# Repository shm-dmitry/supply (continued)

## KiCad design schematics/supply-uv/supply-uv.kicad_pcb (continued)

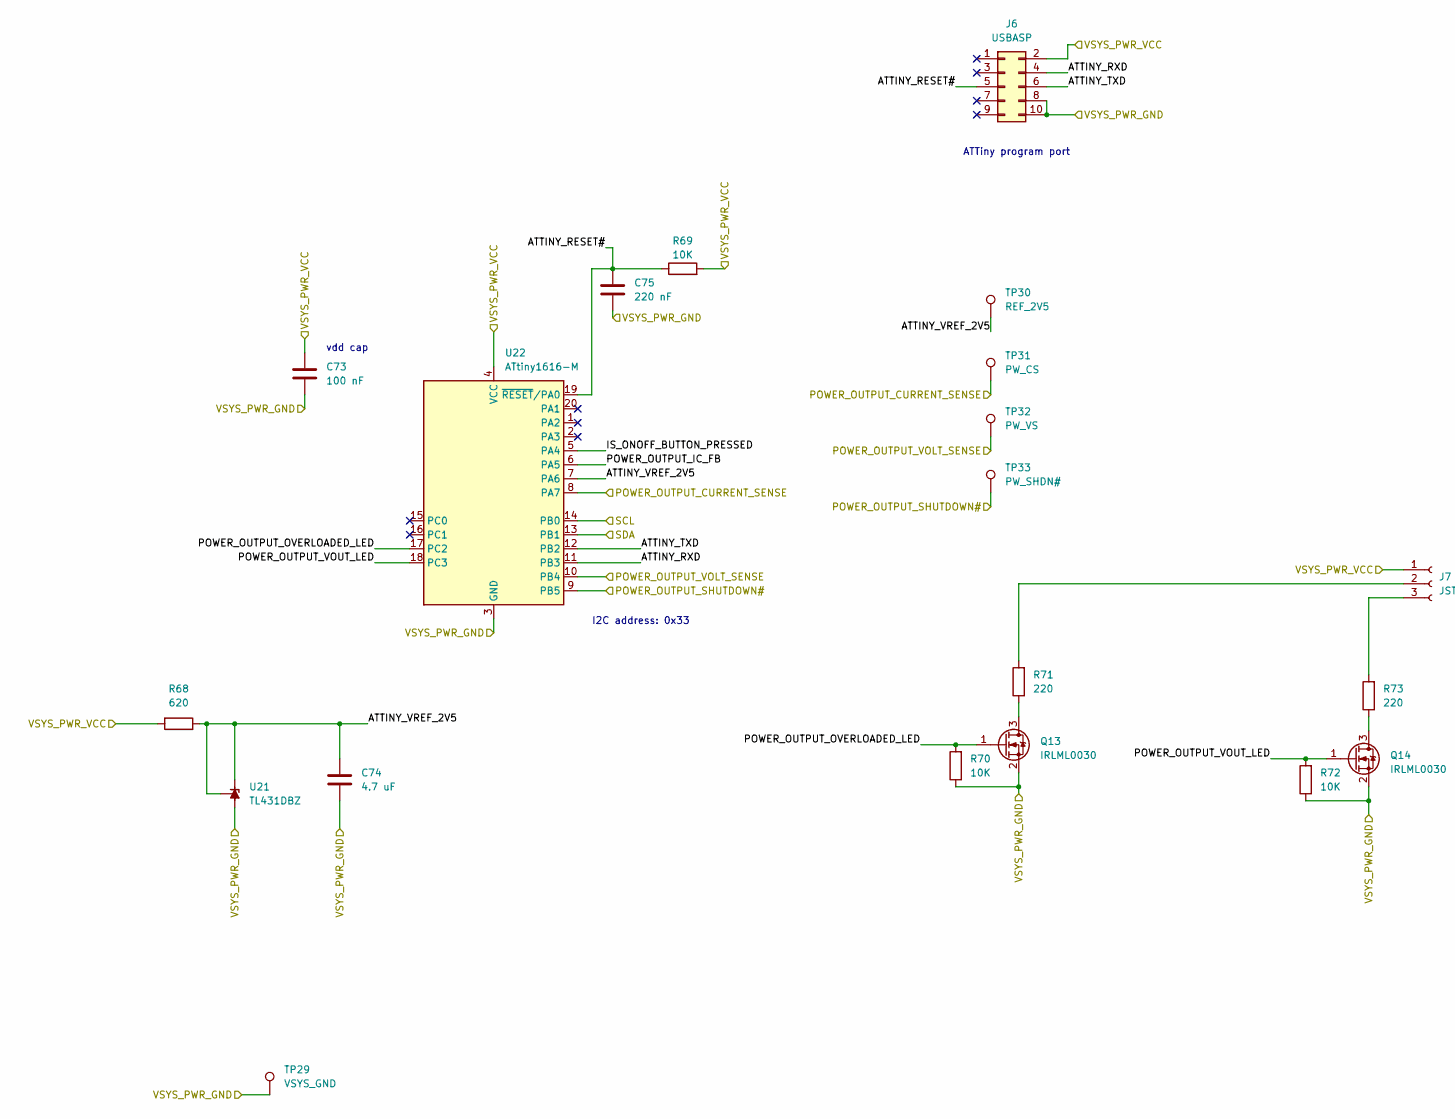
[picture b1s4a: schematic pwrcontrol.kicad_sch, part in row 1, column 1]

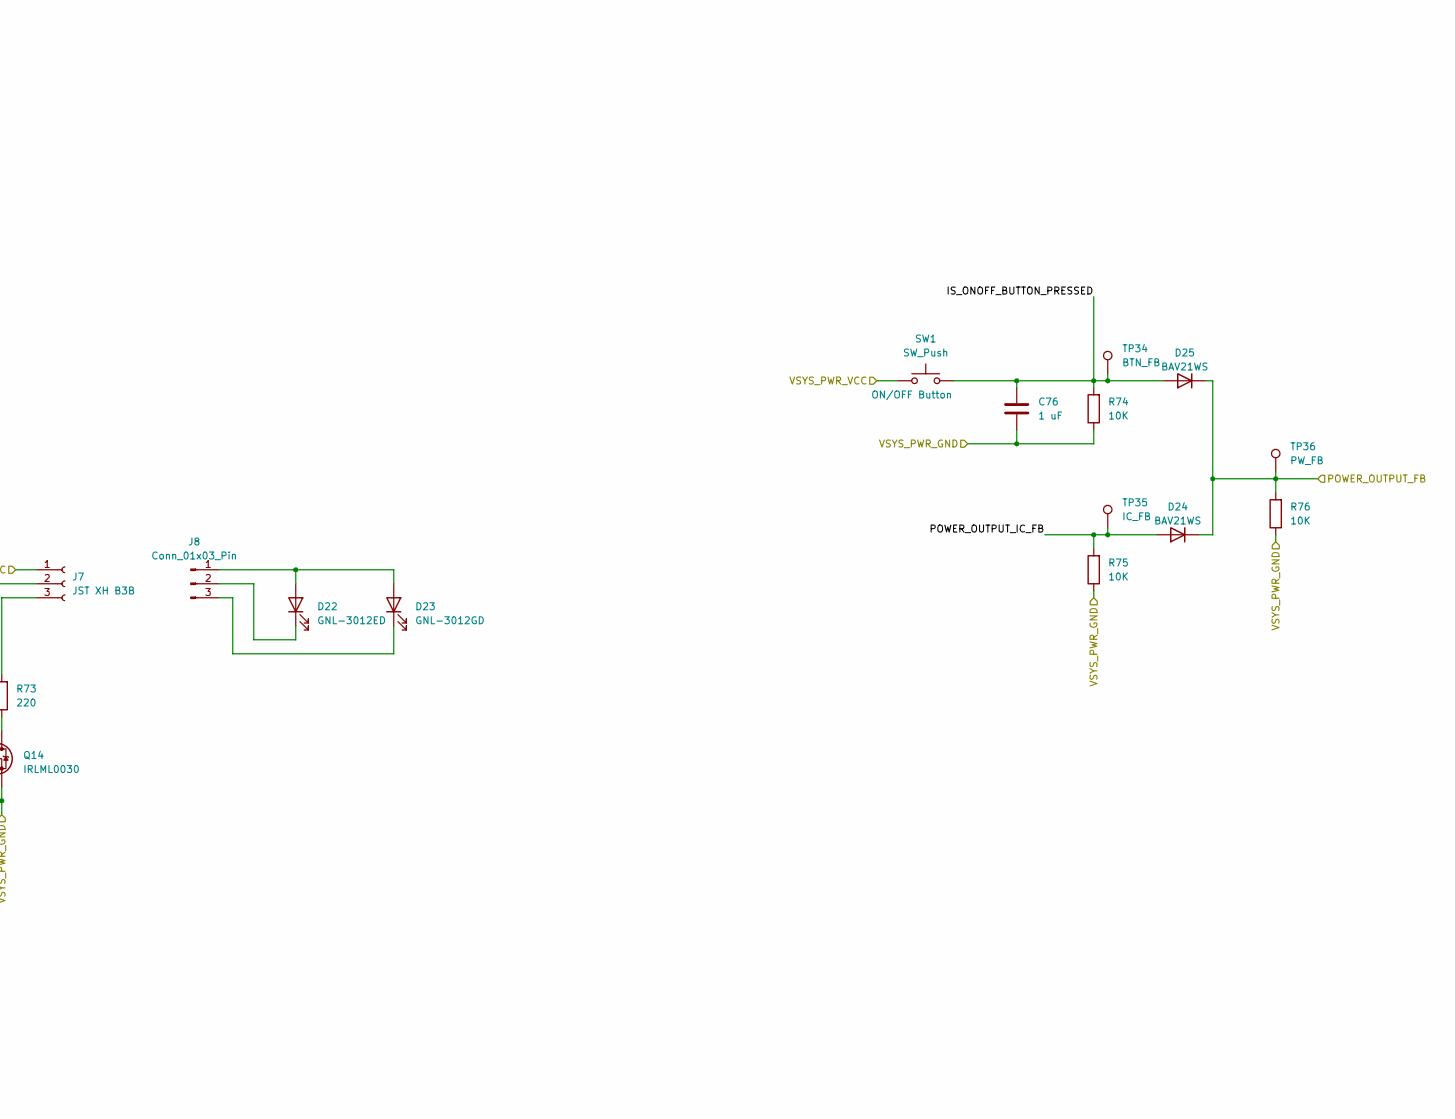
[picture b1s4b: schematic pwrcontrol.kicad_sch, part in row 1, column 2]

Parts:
C73: 100 nF; C_0603_1608Metric
C74: 4.7 uF; C_0603_1608Metric
C75: 220 nF; C_0603_1608Metric
C76: 1 uF; C_0603_1608Metric
D22: GNL-3012ED; JST_XH_B2B-XH-A_1x02_P2.50mm_Vertical
D23: GNL-3012GD; JST_XH_B2B-XH-A_1x02_P2.50mm_Vertical
D24, D25: BAV21WS; D_SOD-323F
J6: USBASP; DC3-2x05_p2.54
J7: JST XH B3B; JST_XH_B3B-XH-A_1x03_P2.50mm_Vertical
J8: Conn_01x03_Pin
Q13, Q14: IRLML0030; SOT-23
R68: 620; R_0805_2012Metric
R69, R70, R72, R74, R75, R76: 10K; R_0805_2012Metric
R71, R73: 220; R_0805_2012Metric
SW1: SW_Push; JST_XH_B2B-XH-A_1x02_P2.50mm_Vertical
TP29: VSYS_GND; TestPoint_Plated_Hole_D1.0mm
TP30: REF_2V5; TestPoint_Pad_1.0x1.0mm
TP31: PW_CS; TestPoint_Pad_1.0x1.0mm
TP32: PW_VS; TestPoint_Pad_1.0x1.0mm
TP33: PW_SHDN#; TestPoint_Pad_1.0x1.0mm
TP34: BTN_FB; TestPoint_Pad_1.0x1.0mm
TP35: IC_FB; TestPoint_Pad_1.0x1.0mm
TP36: PW_FB; TestPoint_Pad_1.0x1.0mm
U21: TL431DBZ; SOT-23
U22: ATtiny1616-M; VQFN-20-1EP_3x3mm_P0.4mm_EP1.7x1.7mm

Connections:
/pwrcontrol Sheet/ATTINY_RESET#: C75.1, J6.5, R69.1, U22.19 (~RESET/PA0)
/pwrcontrol Sheet/ATTINY_RXD: J6.4, U22.11 (PB3)
/pwrcontrol Sheet/ATTINY_TXD: J6.6, U22.12 (PB2)
/pwrcontrol Sheet/ATTINY_VREF_2V5: C74.1, R68.1, TP30.1, U21.1 (K), U21.2 (REF), U22.7 (PA6)
/pwrcontrol Sheet/IS_ONOFF_BUTTON_PRESSED: C76.2, D25.2 (A), R74.2, SW1.2, TP34.1, U22.5 (PA4)
/pwrcontrol Sheet/POWER_OUTPUT_CURRENT_SENSE: TP31.1, U22.8 (PA7); also elsewhere on the board
/pwrcontrol Sheet/POWER_OUTPUT_FB: D24.1 (K), D25.1 (K), R76.2, TP36.1; also elsewhere on the board
/pwrcontrol Sheet/POWER_OUTPUT_IC_FB: D24.2 (A), R75.2, TP35.1, U22.6 (PA5)
/pwrcontrol Sheet/POWER_OUTPUT_OVERLOADED_LED: Q13.1 (G), R70.2, U22.17 (PC2)
/pwrcontrol Sheet/POWER_OUTPUT_SHUTDOWN#: TP33.1, U22.9 (PB5); also elsewhere on the board
/pwrcontrol Sheet/POWER_OUTPUT_VOLT_SENSE: TP32.1, U22.10 (PB4); also elsewhere on the board
/pwrcontrol Sheet/POWER_OUTPUT_VOUT_LED: Q14.1 (G), R72.2, U22.18 (PC3)
unnamed: D22.1 (K), J8.2
unnamed: D22.2 (A), D23.2 (A), J8.1
unnamed: D23.1 (K), J8.3
unnamed: J7.2, R71.2
unnamed: J7.3, R73.2
unnamed: Q13.3 (D), R71.1
unnamed: Q14.3 (D), R73.1

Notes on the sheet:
ATTiny program port
I2C address: 0x33
vdd cap

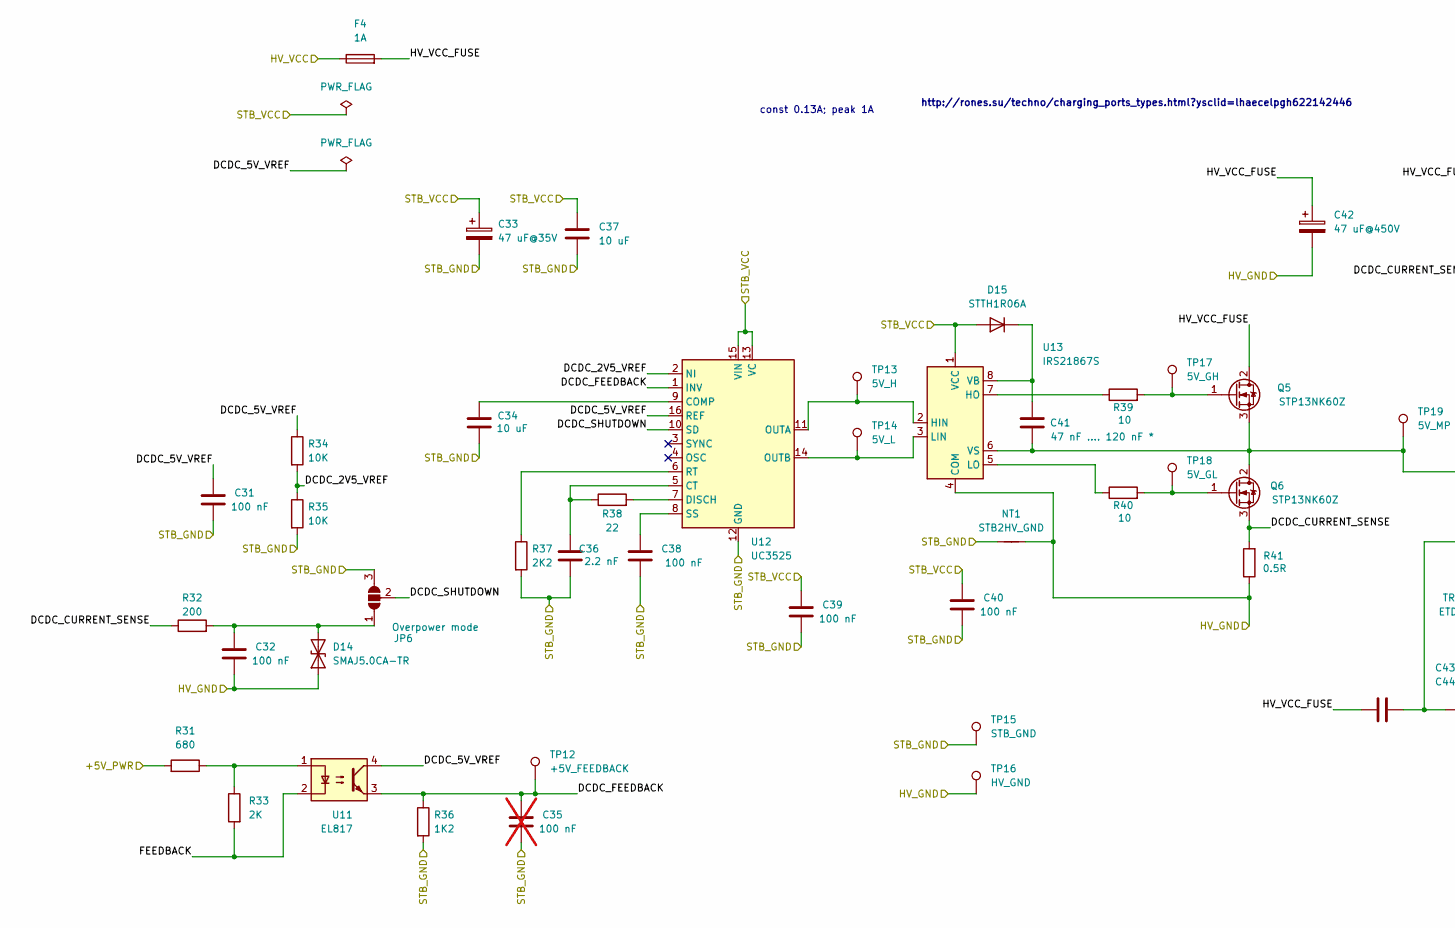
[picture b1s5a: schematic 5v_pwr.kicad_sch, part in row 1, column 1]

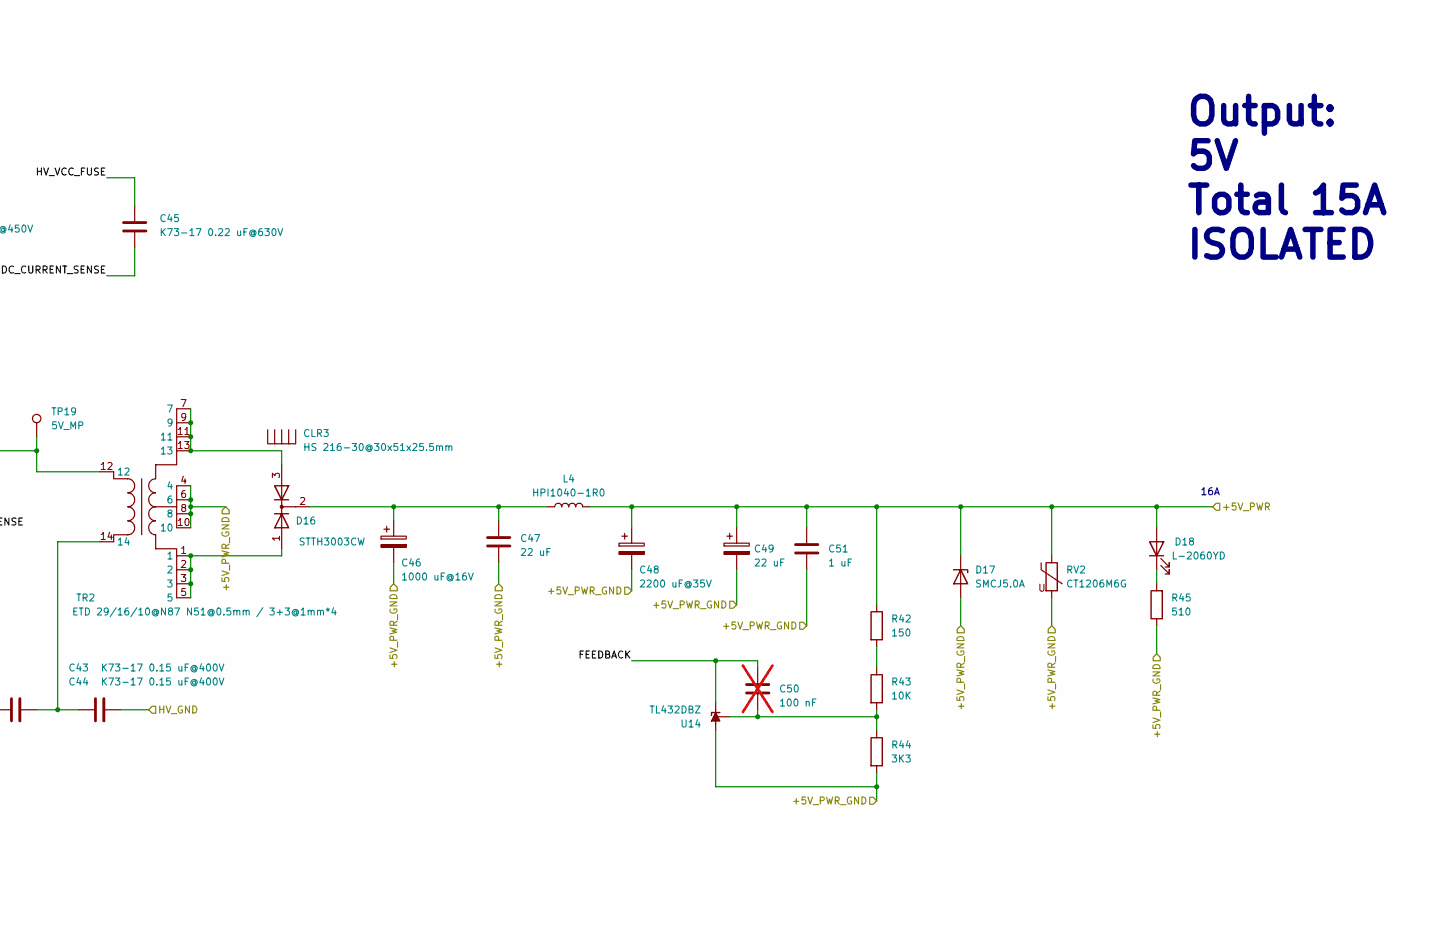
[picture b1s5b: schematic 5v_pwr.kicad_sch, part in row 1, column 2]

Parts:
C31, C32, C38, C39, C40: 100 nF; C_0603_1608Metric
C33: 47 uF@35V; CP_Radial_D6.3mm_P2.50mm
C34, C37: 10 uF; C_0603_1608Metric
C35, C50: 100 nF; C_0603_1608Metric; not fitted
C36: 2.2 nF; C_0603_1608Metric
C41: 47 nF .... 120 nF *; C_0603_1608Metric
C42: 47 uF@450V; CP_Radial_D16.0mm_P7.50mm
C43, C44: К73-17 0.15 uF@400V; C_Rect_L16.5mm_W7.3mm_P15.00mm_MKT
C45: К73-17 0.22 uF@630V; C_Axial_L12.0mm_D6.5mm_P20.00mm_Horizontal
C46: 1000 uF@16V; CP_Radial_D10.0mm_P5.00mm
C47: 22 uF; C_1210_3225Metric
C48: 2200 uF@35V; CP_Radial_D16.0mm_P7.50mm
C49: 22 uF; CP_EIA-3216-10_Kemet-I_Pad1.58x1.35mm_HandSolder
C51: 1 uF; C_0603_1608Metric
CLR3: HS 216-30@30х51х25.5mm; HS 216-30
D14: SMAJ5.0CA-TR; D_SMB
D15: STTH1R06A; D_SMA
D16: STTH3003CW; TO-247-3_Vertical
D17: SMCJ5.0A; D_SMC
D18: L-2060YD; LED_D1.8mm_W3.3mm_H2.4mm
F4: 1A; FuseHolder1808
JP6: Overpower mode; SolderJumper-3_P1.3mm_Bridged2Bar12_RoundedPad1.0x1.5mm_Num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
L4: HPI1040-1R0; Ferrocore-HPI1040
NT1: STB2HV_GND; NetTie-2_SMD_Pad0.5mm
Q5, Q6: STP13NK60Z; TO-220-3_Vertical
R31: 680; R_0805_2012Metric
R32: 200; R_0805_2012Metric
R33: 2K; R_0805_2012Metric
R34, R35, R43: 10K; R_0805_2012Metric
R36: 1K2; R_0805_2012Metric
R37: 2K2; R_0805_2012Metric
R38: 22; R_0805_2012Metric
R39, R40: 10; R_0805_2012Metric
R41: 0.5R; R_2512_6332Metric
R42: 150; R_0805_2012Metric
R44: 3K3; R_0805_2012Metric
R45: 510; R_0805_2012Metric
RV2: CT1206M6G; R_1206_3216Metric
TP12: +5V_FEEDBACK; TestPoint_Pad_1.0x1.0mm
TP13: 5V_H; TestPoint_Pad_1.0x1.0mm
TP14: 5V_L; TestPoint_Pad_1.0x1.0mm
TP15: STB_GND; TestPoint_Plated_Hole_D1.0mm
TP16: HV_GND; TestPoint_Plated_Hole_D1.0mm
TP17: 5V_GH; TestPoint_Pad_1.0x1.0mm
TP18: 5V_GL; TestPoint_Pad_1.0x1.0mm
TP19: 5V_MP; TestPoint_Pad_1.0x1.0mm
TR2: ETD 29/16/10@N87 N51@0.5mm / 3+3@1mm*4; ETD29_7x7_vertical
U11: EL817; DIP-4_W7.62mm
U12: UC3525; SOIC-16W_7.5x10.3mm_P1.27mm
U13: IRS21867S; SOIC-8_3.9x4.9mm_P1.27mm
U14: TL432DBZ; SOT-23-3

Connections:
/5V_PWR Sheet/DCDC_2V5_VREF: R34.2, R35.1, U12.2 (NI)
/5V_PWR Sheet/DCDC_5V_VREF: C31.1, R34.1, U11.4, U12.16 (REF)
/5V_PWR Sheet/DCDC_CURRENT_SENSE: C45.1, Q6.3 (S), R32.1, R41.2
/5V_PWR Sheet/DCDC_FEEDBACK: C35.1, R36.1, TP12.1, U11.3, U12.1 (INV)
/5V_PWR Sheet/DCDC_SHUTDOWN: JP6.2 (C), U12.10 (SD)
/5V_PWR Sheet/FEEDBACK: C50.2, R33.2, U11.2, U14.2 (K)
/5V_PWR Sheet/HV_GND: C32.2, C42.2, C44.1, D14.1 (A1), NT1.2, R41.1, TP16.1, U13.4 (COM); also elsewhere on the board
/5V_PWR Sheet/HV_VCC: F4.1; also elsewhere on the board
/5V_PWR Sheet/HV_VCC_FUSE: C42.1, C43.2, C45.2, F4.2, Q5.2 (D)
/5V_PWR Sheet/STB_GND: C31.2, C33.2, C34.2, C35.2, C36.2, C37.1, C38.2, C39.2, C40.2, JP6.3 (B), NT1.1, R35.2, R36.2, R37.2, TP15.1, U12.12 (GND); also elsewhere on the board
/5V_PWR Sheet/STB_VCC: C33.1, C37.2, C39.1, C40.1, D15.2 (A), U12.13 (VC), U12.15 (VIN), U13.1 (VCC); also elsewhere on the board
/+5V_PWR_GND: C46.2, C47.1, C48.2, C49.2, C51.1, D17.2 (A), R44.2, R45.1, RV2.2, TR2.4, TR2.6, TR2.8, TR2.10, U14.3 (A); also elsewhere on the board
/+5V_PWR_VCC: C48.1, C49.1, C51.2, D17.1 (K), D18.2 (A), L4.2, R31.2, R42.1, RV2.1; also elsewhere on the board
unnamed: C43.1, C44.2, TR2.14
unnamed: C32.1, D14.2 (A2), JP6.1 (A), R32.2
unnamed: C41.1, D15.1 (K), U13.8 (VB)
unnamed: D16.1 (A), TR2.1, TR2.2, TR2.3, TR2.5
unnamed: D16.3 (A), TR2.7, TR2.9, TR2.11, TR2.13
unnamed: C46.1, C47.2, D16.2 (K), L4.1
unnamed: D18.1 (K), R45.2
unnamed: Q5.1 (G), R39.2, TP17.1
unnamed: C41.2, Q5.3 (S), Q6.2 (D), TP19.1, TR2.12, U13.6 (VS)
unnamed: Q6.1 (G), R40.2, TP18.1
unnamed: R31.1, R33.1, U11.1
unnamed: R42.2, R43.1
unnamed: C34.1, U12.9 (COMP)
unnamed: C36.1, R38.1, U12.5 (CT)
unnamed: R38.2, U12.7 (DISCH)
unnamed: TP13.1, U12.11 (OUTA), U13.2 (HIN)
unnamed: TP14.1, U12.14 (OUTB), U13.3 (LIN)
unnamed: R37.1, U12.6 (RT)
unnamed: C38.1, U12.8 (SS)
unnamed: R39.1, U13.7 (HO)
unnamed: R40.1, U13.5 (LO)
unnamed: C50.1, R43.2, R44.1, U14.1 (REF)

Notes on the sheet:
const 0.13A; peak 1A
http://rones.su/techno/charging_ports_types.html?ysclid=lhaecelpgh622142446
16A
Output: 5V Total 15A ISOLATED

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
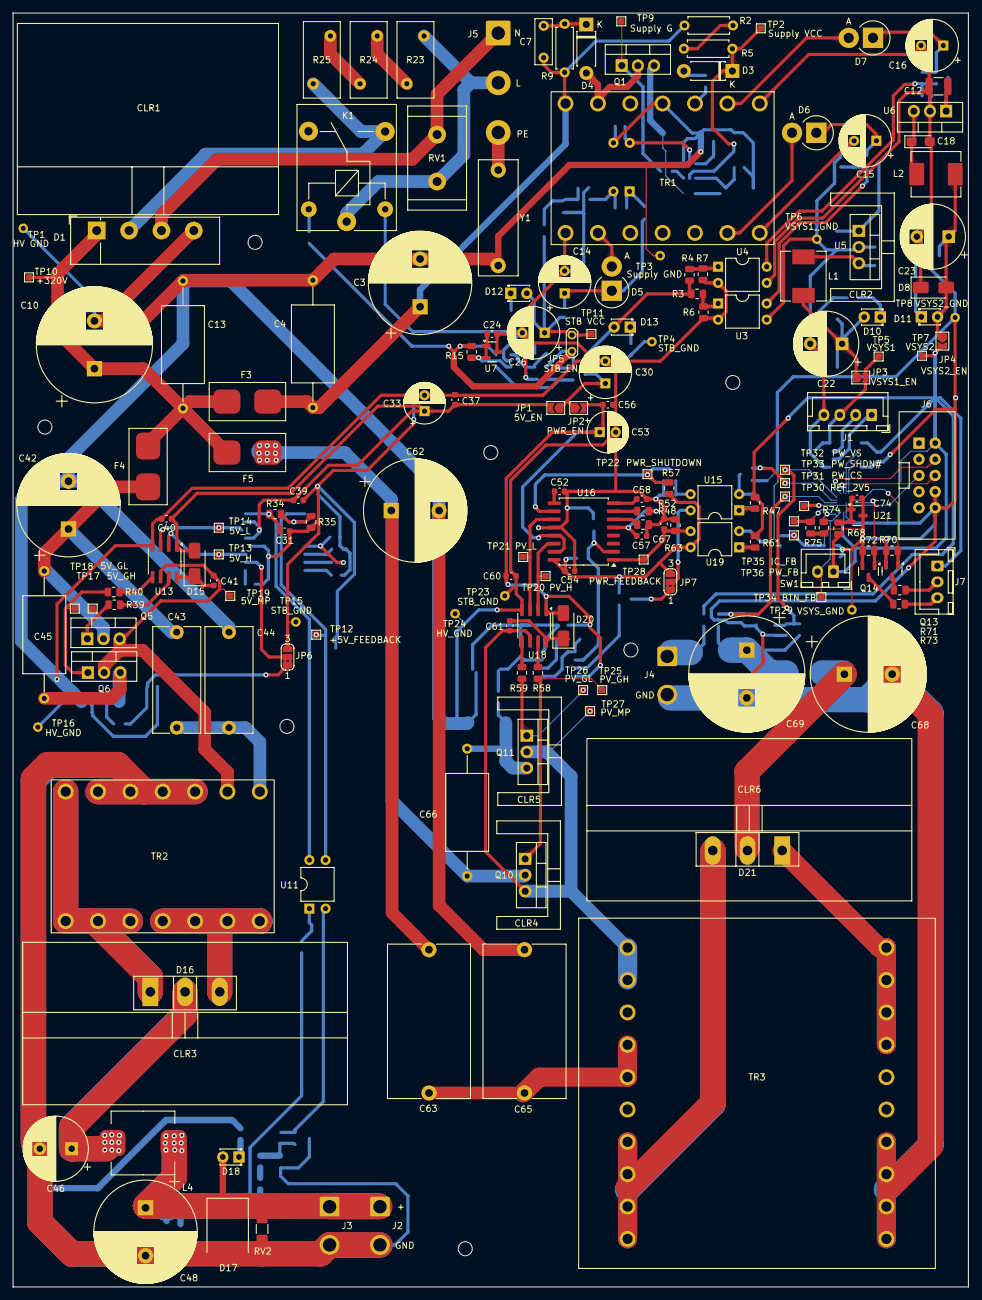
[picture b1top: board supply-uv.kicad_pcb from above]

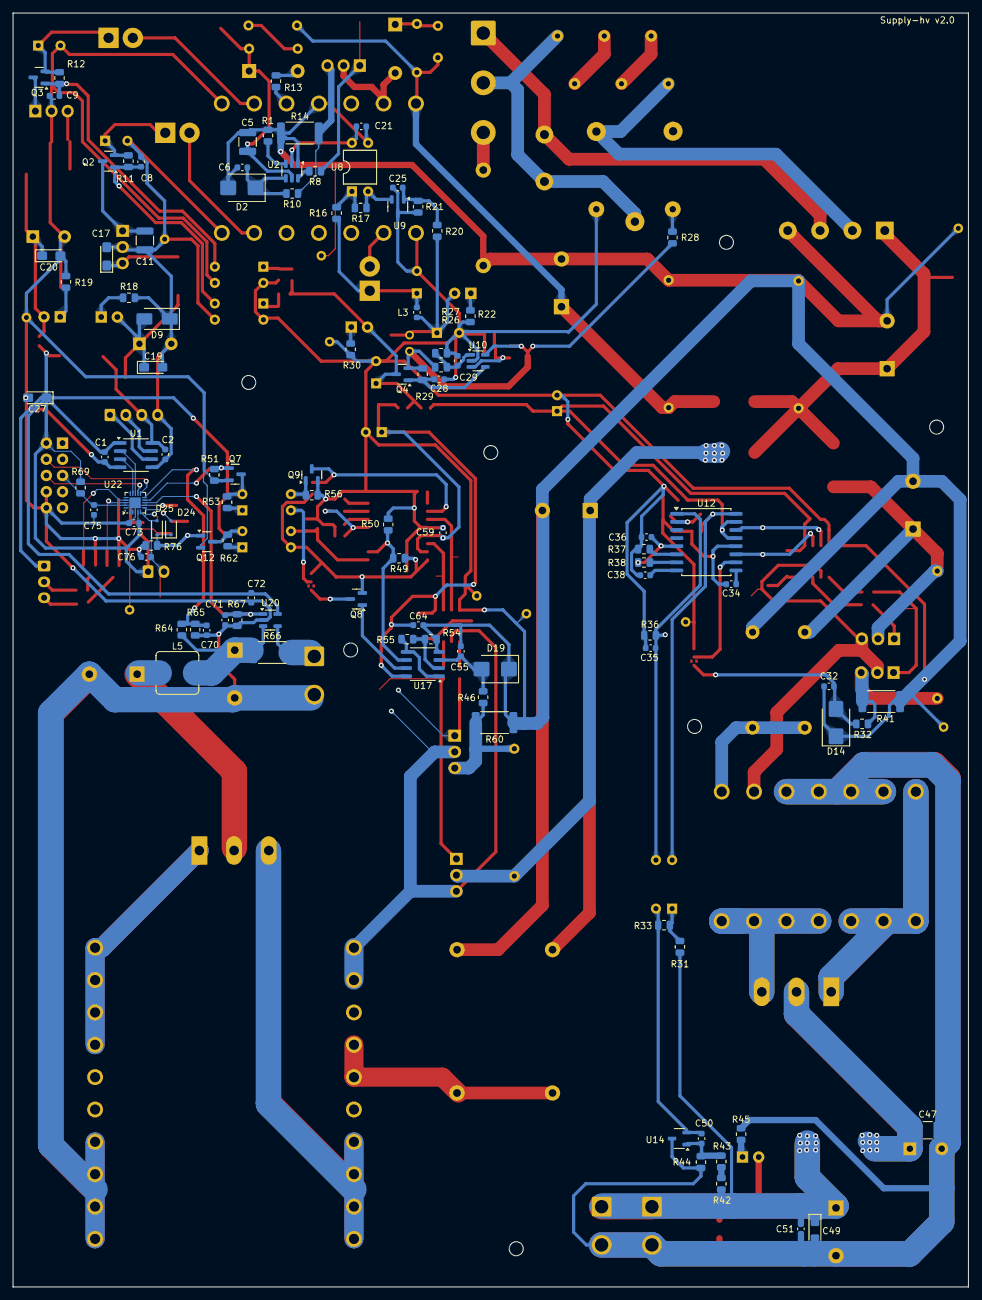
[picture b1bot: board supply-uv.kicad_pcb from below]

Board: 2 copper layers, 150.0 x 200.0 mm, 293 parts (105 on the bottom side), 146 nets.

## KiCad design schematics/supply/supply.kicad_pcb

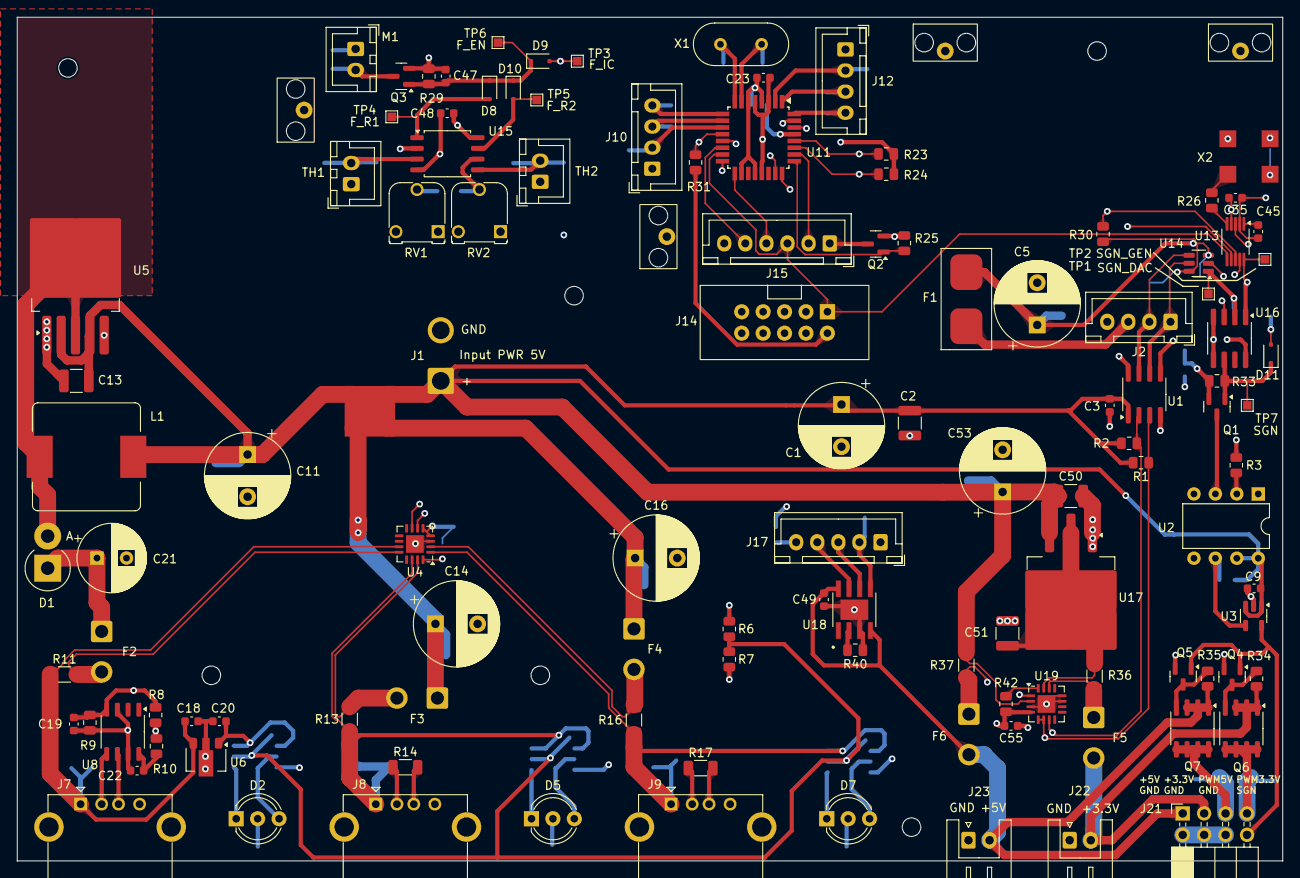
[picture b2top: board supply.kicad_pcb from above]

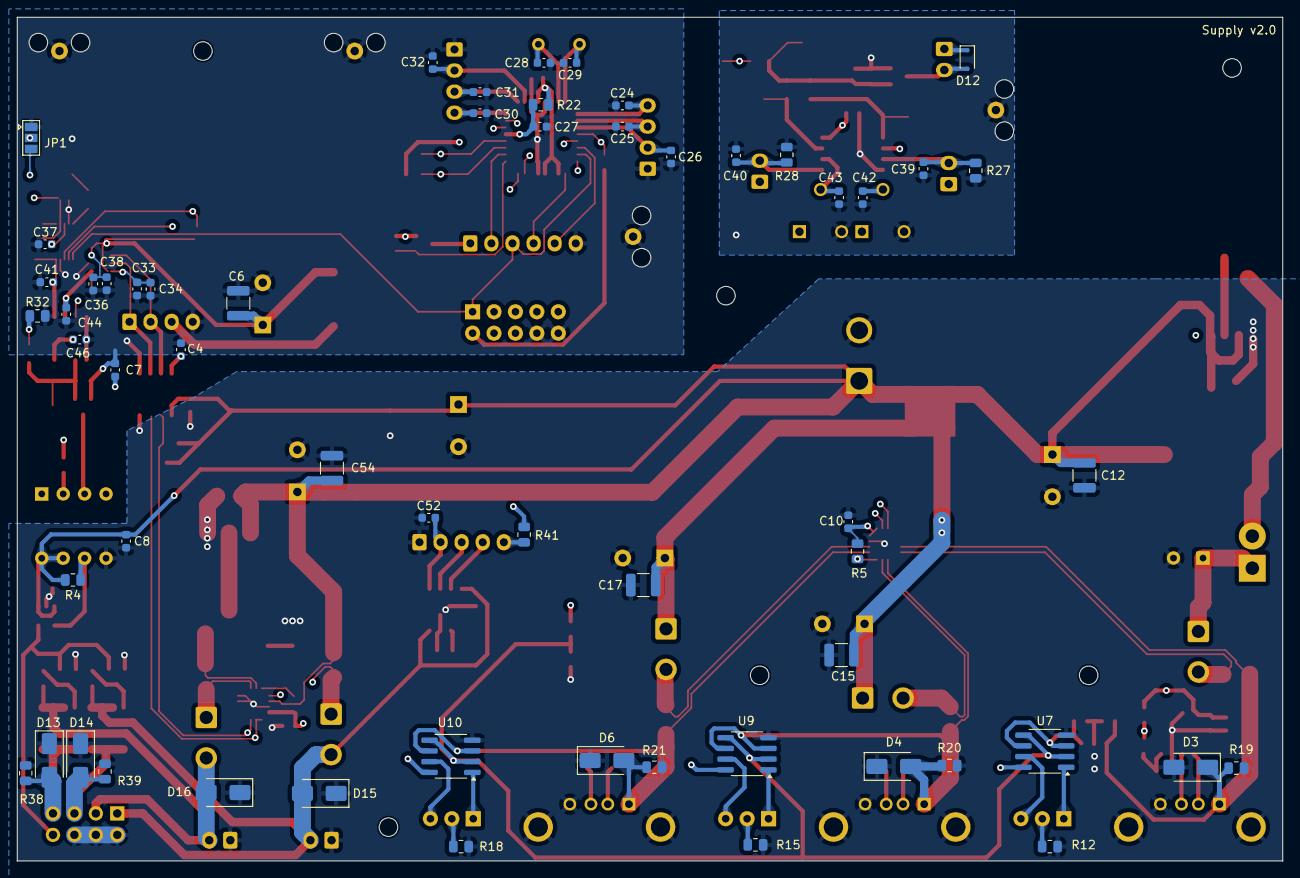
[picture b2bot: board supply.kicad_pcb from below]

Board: 4 copper layers, 150.0 x 100.0 mm, 186 parts (58 on the bottom side), 99 nets.

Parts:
C1, C5, C11, C14, C16, C53: 1000 uF@16V; CP_Radial_D10.0mm_P5.00mm
C2, C6, C12, C13, C15, C17, C50, C51, C54: 22 uF; C_1210_3225Metric
C3, C4, C10, C37, C55: 100 nF; C_0603_1608Metric
C7, C8, C9, C22, C23, C35, C46, C47, C48: 1 uF; C_0603_1608Metric
C18, C20, C33, C36, C49, C52: 10 uF; C_0603_1608Metric
C19, C24, C25, C30, C31, C45: 10 nF; C_0603_1608Metric
C21: 220 uF@35V; CP_Radial_D8.0mm_P3.50mm
C26, C27, C32, C39, C40, C42, C43: 220 nF; C_0603_1608Metric
C28, C29: 15 pF; C_0603_1608Metric
C34, C38, C44: 0.1 uF; C_0603_1608Metric
C41: 22 pF; C_0603_1608Metric
D1: SR540; D_DO-201AD_P3.81mm_Vertical_AnodeUp
D2, D5, D7: red/green, common cathode, F3; LED_D5.0mm-3
D3: SMAJ26A; D_SMA
D4, D6, D13, D14, D15, D16: SMAJ5.0CA-TR; D_SMA
D8, D9, D10, D11, D12: BAV21WS; D_SOD-323F
F1: Fuse; FuseHolder1808
F2: 5A; SolderWire-0.75sqmm_1x02_P4.8mm_D1.25mm_OD2.3mm
F3, F4, F5, F6: 3A; SolderWire-0.75sqmm_1x02_P4.8mm_D1.25mm_OD2.3mm
H1, H2, H3, H4, H5, H6: MountingHole; MountingHole_2.2mm_M2
J1: power +5V connector from board#1; SolderWire-1.5sqmm_1x02_P6mm_D1.7mm_OD3mm
J2: VSYS connector from Board#1; JST_XH_B4B-XH-A_1x04_P2.50mm_Vertical
J3, J4, J5, J6: RFShield_OnePiece; EMI_SHIELD_1P_2H
J7, J8, J9: USB_A
J10, J12: Conn_01x04_Pin; JST_XH_B4B-XH-A_1x04_P2.50mm_Vertical
J14: USBASP; DC3-2x05_p2.54
J15: Conn_01x06_Pin; JST_XH_B6B-XH-A_1x06_P2.50mm_Vertical
J17: Conn_01x05_Pin; JST_XH_B5B-XH-A_1x05_P2.50mm_Vertical
J21: Conn_02x04_Odd_Even; PinSocket_2x04_P2.54mm_Horizontal
J22, J23: jst xh angle; JST_XH_S2B-XH-A_1x02_P2.50mm_Horizontal
JP1: SolderJumper_3_Open; SolderJumper-3_P1.3mm_Open_Pad1.0x1.5mm
L1: AMPLF1260, 4.7 uH; L_TaiTech_TMPC1265_13.5x12.5mm
M1: Fan; JST_XH_B2B-XH-A_1x02_P2.50mm_Vertical
NT1: PWR2LOGIC; NetTie-2_SMD_Pad0.5mm
NT2: +5V->USB; NetTie-4_SMD_Pad2.0mm
NT3: PWR2LOCALPWR; NetTie-2_SMD_Pad2.0mm
Q1, Q3, Q4, Q5: IRLML0030; SOT-23
Q2: IRLML5203; SOT-23
Q6, Q7: IRF7425PbF; SOIC-8_3.9x4.9mm_P1.27mm
R1, R2, R23, R24: 4K7; R_0805_2012Metric
R3: ?; R_0805_2012Metric
R4: 350; R_0805_2012Metric
R5, R6, R7, R19, R20, R21, R22, R25, R29, R30, R31, R32, R42: 10K; R_0805_2012Metric
R8: 100K; R_0805_2012Metric
R9: 33K; R_0805_2012Metric
R10: 2K; R_0805_2012Metric
R11, R13, R16, R36, R37: 0.01; R_1206_3216Metric
R12, R15, R18, R41: 510; R_0805_2012Metric
R14, R17: 0; R_1206_3216Metric
R26: 100; R_0805_2012Metric
R27, R28: 5K1; R_0805_2012Metric
R33, R34, R35, R38, R39, R40: 1K; R_0805_2012Metric
RV1, RV2: RM065, 10K; Potentiometer_Runtron_RM-065_Vertical
TH1, TH2: MF52-502 5K; JST_XH_B2B-XH-A_1x02_P2.50mm_Vertical
TP1: SGN_DAC; TestPoint_Pad_1.0x1.0mm
TP2: SGN_GEN; TestPoint_Pad_1.0x1.0mm
TP3: F_IC; TestPoint_Pad_1.0x1.0mm
TP4: F_R1; TestPoint_Pad_1.0x1.0mm
TP5: F_R2; TestPoint_Pad_1.0x1.0mm
TP6: F_EN; TestPoint_Pad_1.0x1.0mm
TP7: SGN; TestPoint_Pad_1.0x1.0mm
U1: ISO1540; SOIC-8_3.9x4.9mm_P1.27mm
U2: 6N137; DIP-8_W7.62mm
U3: FAN3100; SOT-23-5
U4, U19: INA3221; Texas_RGV0016A_VQFN-16-1EP_4x4mm_P0.65mm_EP2.1x2.1mm
U5: XL6009; TO-263-5_TabPin3
U6: L78L33ACUTR; SOT-89-3
U7, U9, U10: LM158DR; SOP-8_3.76x4.96mm_P1.27mm
U8: IP2163; SOP-8_3.9x4.9mm_P1.27mm
U11: ATmega328-A; TQFP-32_7x7mm_P0.8mm
U13: AD9833xRM; MSOP-10_3x3mm_P0.5mm
U14: MCP4726A0T-E/CH; SOT-23-6
U15: LM158DR; SOP-8_5.28x5.23mm_P1.27mm
U16: MAX961; SOP-8_3.76x4.96mm_P1.27mm
U17: LM1085-3.3; TO-263-3_TabPin2
U18: TP4056; SOP127P600X175-9N
X1: HC-49U, 16MHz; Crystal_HC49-U_Vertical
X2: 25 MHz; Oscillator_SMD_EuroQuartz_XO91-4Pin_7.0x5.0mm

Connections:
/+5V_PWR_GND: C1.2, C2.1, C3.2, C8.2, C9.2, C10.1, C11.2, C12.1, C13.1, C14.2, C15.1, C16.2, C17.1, C18.1, C19.1, C20.1, C21.2, C22.1, C49.1, C50.1, C51.1, C52.1, C53.2, C54.1, C55.1, D3.2 (A2), D4.1 (A1), D6.1 (A1), D13.1 (A1), D14.1 (A1), D15.1 (A1), D16.1 (A1), J1.2, J7.4 (GND), J7.5 (Shield), J8.4 (GND), J8.5 (Shield), J9.4 (GND), J9.5 (Shield), J17.1, J21.2, J21.4, J21.6, J22.1, J23.1, Q4.2 (S), Q5.2 (S), R7.2, R9.2, R12.2, R15.2, R18.2, R19.2, R20.2, R21.2, R38.1, R39.1, R40.1, U1.4 (GND1), U2.5 (GND), U3.2 (GND), U4.3 (GND), U4.17 (EP), U5.1 (GND), U6.2 (GND), U7.4 (V-), U8.3 (GND), U8.7 (SEL), U9.4 (V-), U10.4 (V-), U17.1 (GND), U18.3 (VSS), U18.9 (GND), U19.3 (GND), U19.11 (IN-1), U19.12 (IN+1), U19.17 (EP)
/+5V_PWR_LOGIC: C1.1, C2.2, C3.1, C10.2, C55.2, NT1.2, R1.2, R2.2, R5.1, R6.1, R42.1, U1.1 (VCC1), U4.4 (VS), U4.5 (A0), U7.8 (V+), U9.8 (V+), U10.8 (V+), U19.4 (VS)
/+5V_PWR_VCC: C8.1, C9.1, J1.1, NT1.1, NT2.1, NT3.1, R4.1, U2.7 (EN), U2.8 (VCC), U3.1 (VCC), U3.3 (IN+)
/Control & Fan/ENABLE_FAN: D9.2 (A), TP3.1, U11.23 (PC0)
/Control & Fan/ENCODER_I_A: C30.1, J12.4, U11.32 (PD2)
/Control & Fan/ENCODER_I_B: C31.1, J12.3, U11.1 (PD3)
/Control & Fan/ENCODER_I_CLICK: C32.1, J12.2, U11.2 (PD4)
/Control & Fan/ENCODER_V_A: C24.1, J10.4, U11.9 (PD5)
/Control & Fan/ENCODER_V_B: C25.1, J10.3, U11.10 (PD6)
/Control & Fan/ENCODER_V_CLICK: C26.1, J10.2, U11.11 (PD7)
/Control & Fan/MISO: J14.9, U11.16 (PB4)
/Control & Fan/MOSI: J14.1, J15.3, U11.15 (PB3), U13.6 (SDATA)
/Control & Fan/RESET#: C27.1, J14.5, R22.1, U11.29 (~RESET/PC6)
/Control & Fan/RXD: J14.4, U11.30 (PD0)
/Control & Fan/SCK: J14.7, J15.4, U11.17 (PB5), U13.7 (SCLK)
/Control & Fan/SIGNAL_ALWAYS_ON: D11.2 (A), R32.1, U11.24 (PC1)
/Control & Fan/SIGNAL_CS: R30.1, U11.13 (PB1), U13.8 (~FSYNC)
/Control & Fan/SIGNAL_GEN_SHTDN: R31.1, U11.12 (PB0), U16.3 (SHUTDOWN)
/Control & Fan/SIGNAL_OUT: D11.1 (K), Q1.1 (G), R33.2, TP7.1, U16.6 (Q)
/Control & Fan/TFT_CS: J15.5, U11.14 (PB2)
/Control & Fan/TFT_DC: J15.2, U11.26 (PC3)
/Control & Fan/TFT_ENABLE#: Q2.1 (G), R25.1, U11.25 (PC2)
/Control & Fan/TXD: J14.6, U11.31 (PD1)
/Output connectors/3.3V_FUSE: D16.2 (A2), F5.2, J21.3, J22.2, Q6.1 (S), Q6.2 (S), Q6.3 (S), R34.2
/Output connectors/3V3_-: F5.1, R36.1, U19.14 (IN-2)
/Output connectors/5V_-: F6.1, R37.1, U19.1 (IN-3)
/Output connectors/5V_FUSE: C49.2, D15.2 (A2), F6.2, J21.1, J23.2, Q7.1 (S), Q7.2 (S), Q7.3 (S), R35.2, U18.4 (VIN), U18.8 (EN)
/Output connectors/+3V3: C51.2, R36.2, U17.2 (VO), U19.15 (IN+2)
/Output connectors/+5V: C50.2, C53.1, C54.2, NT3.2, R37.2, R41.1, U17.3 (VI), U19.2 (IN+3)
/Output connectors/LIION_CHARGE_LED1: J17.4, U18.7 (STAT1)
/Output connectors/LIION_CHARGE_LED2: J17.3, U18.6 (STAT2)
/Output connectors/LIION_CHARGE_VBAT: C52.2, J17.2, U18.5 (VBAT)
/Output connectors/SIGNAL_OUT: J21.8, Q4.1 (G), Q5.1 (G), U3.5 (OUT)
/Output connectors/SIGNAL_OUT_PWR_3V3: D13.2 (A2), J21.7, Q6.5 (D), Q6.6 (D), Q6.7 (D), Q6.8 (D), R38.2
/Output connectors/SIGNAL_OUT_PWR_5V: D14.2 (A2), J21.5, Q7.5 (D), Q7.6 (D), Q7.7 (D), Q7.8 (D), R39.2
/PWR_SCL: R1.1, U1.3 (SCL1), U4.6 (SCL), U19.5 (A0), U19.6 (SCL)
/PWR_SDA: R2.1, U1.2 (SDA1), U4.7 (SDA), U19.7 (SDA)
/VSYS_GND: C4.2, C5.2, C6.1, C7.2, C23.2, C24.2, C25.2, C26.2, C27.2, C28.2, C29.2, C30.2, C31.2, C32.2, C33.2, C34.2, C35.2, C36.2, C37.1, C38.2, C39.1, C40.1, C41.2, C42.1, C43.1, C44.2, C46.2, C47.1, C48.2, J2.4, J3.1 (Shield), J4.1 (Shield), J5.1 (Shield), J6.1 (Shield), J10.1, J12.1, J14.8, J14.10, J15.6, JP1.1 (A), Q1.2 (S), Q3.2 (S), R27.1, R28.1, R29.1, R32.2, R33.1, RV1.3, RV2.3, U1.5 (GND2), U11.3 (GND), U11.5 (GND), U11.21 (GND), U13.4 (DGND), U13.9 (AGND), U14.2 (GND), U15.4 (V-), U16.4 (LATCH_EN), U16.5 (GND), X2.2 (GND)
/VSYS_SCL: J2.1, R23.1, U1.6 (SCL2), U11.28 (PC5), U14.5 (SCL)
/VSYS_SDA: J2.2, R24.1, U1.7 (SDA2), U11.27 (PC4), U14.4 (SDA)
/VSYS_VCC: F1.1, J2.3
/VSYS_VCC_FUSE: C4.1, C5.1, C6.2, C7.1, C23.1, C33.1, C34.1, C35.1, C36.1, C38.1, C45.2, C46.1, C48.1, D12.1 (K), F1.2, J14.2, JP1.3 (B), M1.1 (+), Q2.2 (S), R3.2, R22.2, R23.2, R24.2, R25.2, R30.2, R31.2, RV1.1, RV2.1, TH1.1, TH2.1, U1.8 (VCC2), U11.4 (VCC), U11.6 (VCC), U11.18 (AVCC), U11.20 (AREF), U13.2 (VDD), U14.3 (VDD), U14.6 (VREF), U15.8 (V+), U16.8 (VCC), X2.4 (Vcc)
/usb ports/DCDC_CLR_PAD: D1.2 (A), L1.1, U5.3 (SW)
/usb ports/USB_1_+5V: C11.1, C12.2, C13.2, L1.2, NT2.3, U5.2 (EN), U5.4 (VIN)
/usb ports/USB_1_BP: C21.1, D1.1 (K), F2.1, R8.1, R10.2
/usb ports/USB_1_D+: J7.3 (D+), U8.6 (DP)
/usb ports/USB_1_D-: J7.2 (D-), U8.5 (DM)
/usb ports/USB_2_+5V: C14.1, C15.2, F3.1, NT2.4
/usb ports/USB_3_+5V: C16.1, C17.2, F4.1, NT2.2
/usb ports/VBUS1_3.3V: C20.2, U6.1 (OUT), U7.3 (+), U7.6 (-)
/usb ports/VBUS_1: C18.2, D3.1 (A1), J7.1 (VBUS), R11.1, R19.1, U4.11 (IN-1), U6.3 (IN)
/usb ports/VBUS_1_+: F2.2, R11.2, U4.12 (IN+1)
/usb ports/VBUS_2: D4.2 (A2), J8.1 (VBUS), R13.1, R20.1, U4.14 (IN-2), U9.3 (+), U9.6 (-)
/usb ports/VBUS_2_+: F3.2, R13.2, U4.15 (IN+2)
/usb ports/VBUS_3: D6.2 (A2), J9.1 (VBUS), R16.1, R21.1, U4.1 (IN-3), U10.3 (+), U10.6 (-)
/usb ports/VBUS_3_+: F4.2, R16.2, U4.2 (IN+3)
/usb ports/VREF_2V5: R6.2, R7.1, U7.2 (-), U7.5 (+), U9.2 (-), U9.5 (+), U10.2 (-), U10.5 (+)
unnamed: D2.1 (A1), U7.1
unnamed: D2.3 (A2), U7.7
unnamed: D2.2 (K), R12.1
unnamed: D5.1 (A1), U9.1
unnamed: D5.3 (A2), U9.7
unnamed: D5.2 (K), R15.1
unnamed: D7.1 (A1), U10.1
unnamed: D7.3 (A2), U10.7
unnamed: D7.2 (K), R18.1
unnamed: D8.2 (A), TP4.1, U15.1
unnamed: D10.2 (A), TP5.1, U15.7
unnamed: C47.2, D8.1 (K), D9.1 (K), D10.1 (K), Q3.1 (G), R29.2, TP6.1
unnamed: D12.2 (A), M1.2 (-), Q3.3 (D)
unnamed: J8.3 (D+), R14.2
unnamed: J8.2 (D-), R14.1
unnamed: J9.3 (D+), R17.2
unnamed: J9.2 (D-), R17.1
unnamed: J15.1, Q2.3 (D)
unnamed: J17.5, R41.2
unnamed: JP1.2 (C), X2.1 (OE)
unnamed: Q1.3 (D), U2.3 (C)
unnamed: Q4.3 (D), Q6.4 (G), R34.1
unnamed: Q5.3 (D), Q7.4 (G), R35.1
unnamed: R3.1, U2.2 (A)
unnamed: R4.2, U2.6 (VO), U3.4 (IN-)
unnamed: R5.2, U4.16 (VPU)
unnamed: C19.2, R8.2, R9.1, U5.5 (FB), U8.4 (FB)
unnamed: C22.2, R10.1, U8.8 (VBUS)
unnamed: C28.1, U11.7 (XTAL1/PB6), X1.2
unnamed: C29.1, U11.8 (XTAL2/PB7), X1.1
unnamed: C37.2, U13.3 (CAP/2.5V)
unnamed: C45.1, U13.1 (COMP)
unnamed: R26.1, U13.5 (MCLK)
unnamed: C41.1, TP2.1, U13.10 (VOUT), U16.1 (IN+)
unnamed: C44.1, TP1.1, U14.1 (VOUT), U16.2 (IN-)
unnamed: C39.2, R27.2, TH1.2, U15.3 (+)
unnamed: C42.2, RV1.2, U15.2 (-)
unnamed: C40.2, R28.2, TH2.2, U15.5 (+)
unnamed: C43.2, RV2.2, U15.6 (-)
unnamed: R40.2, U18.2 (ISET)
unnamed: R42.2, U19.16 (VPU)
unnamed: R26.2, X2.3 (OUT)

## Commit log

2023-06-29 created boards
2023-07-07 prepare to replace ina228 to attiny16+ina169(?). ina228 is an intresting chip, but its too expensive and Im not sure I can buy it on ali
2023-07-11 Prepare to move USB ports to a few millimenters outside
2023-07-11 Updated boards
2023-07-12 little changes in schematics
2023-07-12 prepare to add current measurement for a middle-current 5V and 3.3V lines
2023-07-13 prepare to replace inductor on 5V power line
2023-07-13 Added over-voltage protection to 5V line
2023-07-17 Fixed problem with 20V on one leg of comparator
2023-07-17 Some changes in board - Im preparing it to production
2023-07-17 Changed fuse on 400V line
2023-07-19 Board prepared to order
2023-07-19 Created gerber-files to check order cost
2023-07-24 One board settings changed from 4-layers to 2-layers to reduce it's price
2023-07-24 Project splited to 2 sub-projects - I want to reduce board production price
2023-07-24 UV board size changed to 100x100 to reduce production price
2023-07-25 Added Li-Ion charger port
2023-08-07 Boards prepared to order
2023-09-18 First firmware (not tested)
2023-09-19 First firmware works on simulator
2023-09-20 main firmware - ready to write UI
2023-09-21 Firmware ready?
2023-09-22 Some UI fixes
2023-10-18 Found and fixed issues in schematics.
2023-10-19 standby & pfc almost works
2023-10-21 Some changes
2023-10-23 Preapare firmwware to upload on device
2023-10-24 fix pins in firmware
2023-10-31 Continue soldering and setting up hardware
2023-10-31 supply-uv, new board ordered
2023-11-05 Board fixes
2023-11-05 Fix reading current from INA3221
2023-11-16 supply board - power controllers changed; PWM logic changed
2023-11-18 re-design supply board
2023-12-28 Fixed error on board, v1.3 ordered
2024-03-07 Continue project
2024-04-04 some changes in schema. I found additional error. This commit saves changes before re-write some blocks
2024-06-24 debugging DCDC converters... Standby supply works fine (noise level = 1,7%). At now Starting to debug PFC module
2024-06-28 I cant fix problem with 2MHZ@3V noise under 5V section. It came from POWER GND line (common for standby supply & 400V line). So, I make desision to rewrite schema
2024-07-01 new calculation
2024-07-01 first schema version for board-uv
2024-07-02 Board#1 schematics rewrited
2024-07-03 added some protection logic
2024-07-03 changed operation amplifier
2024-07-03 start board#1 tracing
2024-07-04 First board routing completed. I will review it few days later and maybe optimize something, but base worki done
2024-07-08 first board routed
2024-07-10 some changes in board routing
2024-07-10 gerber files
2025-02-08 power board works (except power output driver, not tested yet), I ready to solder control board
